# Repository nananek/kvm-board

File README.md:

# serial-km-emulator — CH9329 USB キーボード/マウスエミュレータ

MR-CH9329EMU-USB（マルツの CH9329 モジュール）の代替を JLCPCB の SMT 実装で作るための KiCad プロジェクトです。シリアル側とキーボード/マウス側の両方を USB Type-C にしています。

- 基板: 57.6 × 31.4 × 1.6 mm、2 層。実物の FRISK ケース内寸（67.0 × 32.4 mm）の左側に 0.5 mm ずつ逃がして置き、右側はラッチ張り出しとのクリアランスを残した寸法です
- 回路図: [docs/schematic.pdf](docs/schematic.pdf)
- データシートとシルクの対応: [docs/datasheets.md](docs/datasheets.md)
- 配線図: [docs/pcb_routing.png](docs/pcb_routing.png)（GND ベタを消して配線を見やすくしたもの）
- 部品: 21 点、10 種類。すべて JLCPCB の在庫部品（2026-10 時点）。このほかに、実装しないテストパッドを 2 点置いています
- ファームウェア不要。CH9329 の内蔵ファームで動きます

## 仕様

| 項目 | 内容 |
| --- | --- |
| 基板寸法 | 57.6 × 31.4 mm、t1.6 mm、2 層 |
| コネクタ | USB Type-C レセプタクル ×2（HRO TYPE-C-31-M-12）。どちらも基板左端、上下に 5.0 mm ずつ振り分け |
| J1 (SERIAL) | CH340N 経由の USB シリアル。制御側 PC に接続 |
| J2 (HID) | CH9329 の USB HID。操作対象の PC に接続 |
| 給電 | どちらの Type-C からでも給電可。BAT54WS でダイオード OR |
| シリアル | 9600 bps / 8N1（CH9329 出荷時設定） |
| 動作モード | CH9329 Mode 0（キーボード + マウス + カスタム HID の複合デバイス）、プロトコルモード |
| 表示 | ACT# の LED（HID 側の USB 設定完了で点灯） |
| テストパッド | TP1 (SET) / TP2 (GND)。CH9329 の設定変更用 |
| シルク | 表: 部品名とピン極性、裏: リポジトリの QR コード |

J1/J2 はどちらもデバイス側（CC に 5.1k の Rd）です。ホスト PC とは C-to-C でも C-to-A でも接続できます。充電器は接続しないでください。

基板裏面にはリポジトリ（<https://github.com/nananek/serial-km-emulator>）の QR コードをシルクで入れています。ケースに組み込む前ならスマートフォンで読み取れます。

## 回路

```
制御側 PC ──Type-C(J1)── CH340N ──UART── CH9329 ──Type-C(J2)── 操作対象 PC
                              (TXD→RXD, RXD←TXD, 9600 8N1)
```

- CH9329: 5 V 給電。V33 に 0.1 µF、VCC に 0.1 µF。内蔵発振なので水晶なし。
- CH340N: 5 V 給電。V3 に 0.1 µF。内蔵クロックなので水晶なし。
- ESD: 各ポートに USBLC6-2SC6。クランプ用の VBUS ピンは各ポートのローカル VBUS に接続し、100nF (C6/C7) で GND にデカップリング。
- 5 V は BAT54WS ×2 で OR 接続。IC には約 4.7 V が入ります（CH340N の最低 4.0 V、CH9329 の最低 3.7 V の範囲内）。
- CH9329 の MODE0/MODE1、CFG0/CFG1、DEF、RST は未接続。内蔵プルアップ/プルダウンで Mode 0・プロトコルモード・9600 bps になります。UP は 5 V 動作なので未接続です。
- SET はテストパッド TP1 に、GND は TP2 に引き出しています。

### 設定の書き換え（TP1 / TP2）

U1 の右側に 1.7 mm のテストパッドを 2 つ出しています。

| パッド | 接続 | 位置 |
| --- | --- | --- |
| TP1 | CH9329 SET (pin 11) | U1 の右側、左のパッド |
| TP2 | GND | U1 の右側、右のパッド |

ピッチは 2.54 mm です。ピンセットやジャンパワイヤで TP1 と TP2 を短絡したまま、J1 側から WCH の設定ツールで書き換えます。書き換えが終わったら短絡を外してください。通常動作では SET は内蔵プルアップのままです。

## 部品表

`fab/bom_jlcpcb.csv` がそのまま JLCPCB の BOM です。

| 記号 | 値 | パッケージ | LCSC | 備考 |
| --- | --- | --- | --- | --- |
| J1, J2 | TYPE-C-31-M-12 | USB-C 16P | C165948 | HRO |
| U1 | CH9329 | SOP-16 | C2838834 | WCH |
| U2 | CH340N | SOP-8 | C2977777 | WCH |
| D1, D2 | BAT54WS | SOD-323 | C22629 | ショットキー |
| D3, D4 | USBLC6-2SC6 | SOT-23-6 | C7519 | ESD |
| R1–R4 | 5.1k | 0603 | C23186 | CC 用 |
| R5 | 1k | 0603 | C21190 | LED 用 |
| C1–C4, C6, C7 | 100nF | 0603 | C14663 | 50V X7R |
| C5 | 10uF | 0805 | C15850 | 25V X5R |
| LED1 | KT-0603R | 0603 | C2286 | 赤 |

基本部品（C23186、C21190、C14663、C15850、C2286）以外の 5 種類は拡張部品です。拡張部品は 1 種類あたりの実装手数料がかかります。

## JLCPCB での発注

基板:

- 2 層、57.6 × 31.4 mm、t1.6 mm、FR-4、HASL、1 oz
- 最小配線幅/間隔 0.15/0.15 mm、ビア 0.5/0.3 mm。データ線のエスケープに 0.35/0.15 mm のビアも使っています。JLCPCB の標準能力内です。

実装:

- 表面のみ、21 点。
- アップロードするファイル:
  - ガーバー: `fab/serial-km-emulator-gerbers.zip`
  - BOM: `fab/bom_jlcpcb.csv`
  - CPL: `fab/cpl_jlcpcb.csv`
- ガーバー、ドリル、CPL はすべて基板左下を原点にした座標です（KiCad のドリル/配置原点を使用）。ガーバー zip と CPL はセットで再アップロードしてください。JLCPCB の部品ライブラリ向けの回転補正を入れてあります（SO-8/SO-16 +270°、SOT-23-6 +270°。Type-C、SOD-323、LED、0603 は回転補正なし）。Type-C は基板側でフットプリントを 180° 回して開口を左外側、SMT パッドを基板内側に置いています。CPL は JLC 側の原点に合わせて X を 1.571 mm 補正しており、出力は J1/J2 とも 270°、位置はどちらも X 3.7 mm（Y は J1 20.7 mm、J2 10.7 mm）です。補正値は `scripts/make_jlc_files.py` にあります。実装プレビューで向きを確認してください。

注意:

- Type-C コネクタ (C165948) はシェル固定タブが THT 形状ですが、JLCPCB の SMT 実装部品リストに含まれている部品です。SMT 実装で発注できます。
- Type-C の VBUS パッドから 0.5/0.3 mm のビアをパッドの外側に置き、B.Cu で引き回しています。ビアはパッド内ではないため、via-in-pad の DFM 指摘はありません。VBUS は 2 接点ずつパッドが重なっているので、ビアは各コネクタ 2 個です。
- ガーバーは KiCad 10 の既定（X2、4.6 フォーマット）です。

## フリスクケースへの組み込み

基板外形は、実物の FRISK ケースの内寸からラッチ張り出しの分だけ右側をまっすぐ切り落とした **57.6 × 31.4 mm** です。左上・左下・右下の角は **2 mm の 45° パンチカット**で落とし、右上だけ直角に残しています。角丸のルーター加工より外形カットを安くするためです。

### 実寸確認用シート

紙に印刷してケースとの寸法を確認するときは [docs/print_check_a4.pdf](docs/print_check_a4.pdf) を使ってください。

- A4 横、1:1。印刷時は「実際のサイズ / 100%」を選び、「用紙に合わせる」は使わないでください。
- グレーベタが基板、その外側の明るいグレーの帯がケース内壁との 0.5 mm クリアランスです。切り抜いてトレイに落とせます。
- 右側の網掛けがケースのラッチ張り出しです。基板のまっすぐな右辺は、この張り出しから 0.5 mm 離して置きます。
- 下部の 100 mm 目盛りが 100 mm になっていなければ、印刷倍率がずれています。
- `python3 scripts/gen_print_sheet.py` で作り直せます（基板外形は `serial-km-emulator.kicad_pcb` の Edge.Cuts から読みます）。

### ケース寸法

2026-10 に実物の FRISK ケースを実測しました。

- 内寸: **67.0 × 32.4 mm**
- ケース肉厚: **1.0 mm**
- ラッチ張り出しの奥行き: **8.4 mm**
- ラッチ張り出しの高さ: **21.4 mm**（反対側の開口部は 11.0 mm）

基板は内寸から 0.5 mm ずつ逃がしたうえで、右側のラッチ張り出し 8.4 mm を避けるために **57.6 × 31.4 mm** にしています。右辺はラッチ用の切り欠きやローブを作らず、1 本の直線カットです。左上・左下・右下の角は 2 mm の 45° パンチカットで落とし、右上だけ直角に残します。基板をトレイの左・上・下に 0.5 mm ずつ寄せると、右辺はラッチ張り出しから 0.5 mm 離れ、トレイ右側の 8.9 mm は空きます。

参考として、公開されている 3D モデル（[FRISK-CASE.zip](https://try3dcg.world.coocan.jp/files/FRISK-CASE.zip)、`FRISK_CASE1.stl`）は内トレイ 66.4 × 32.4 mm、張り出し 7.8 × 20.3 mm でした。実物は長辺が 0.6 mm 大きいため、実測値を優先しています。モデル配布ページは [3D PRINT用モデルデータ — FRISK CASE](https://try3dcg.world.coocan.jp/note/3dPrint/3dPrint.html#FRISK-CASE) です。

ロット差があるため、初回は必ず現物合わせで確認してください。

### 基板の向きと切り欠き

- 基板のまっすぐな右辺をケースのラッチ張り出し側に向け、基板をトレイの左・上・下に 0.5 mm ずつ寄せて置きます。右辺と張り出しの間に 0.5 mm の隙間ができます。ラッチ用の切り欠きはありません。ケースの角の丸みは、左上・左下・右下の 2 mm パンチカットで逃がします（右上は直角のままです）。
- J1 (SERIAL) と J2 (HID) はどちらも基板左端にあり、上から **10.7 mm** と **20.7 mm** の位置（基板の y 方向中心 15.7 mm から 5.0 mm ずつ、ピッチ 10.0 mm）です。口は基板端から **1.5 mm** 外へ出ます。2 つの口は蓋の切り欠きに収まる位置にあるため、蓋は削らず、トレイ左側壁に約 20 × 4 mm の開口を **壁を貫通するように** 1 か所開けてください（2 つの口が 1.06 mm しか離れていないため、開口も 1 つに繋がります）。
- 基板端はケース内壁から 0.5 mm、肉厚は 1.0 mm なので、1.5 mm の口はケース外面とほぼ面一になります。プラグは壁の切り欠きを通ってコネクタに届きます。
- 切り欠きの外側を 0.3 mm 程度面取りすると、プラグの樹脂（オーバーモールド）が当たりにくくなり、奥まで挿しやすくなります。
- 基板は左・上・下の 0.5 mm を保って固定してください。右側に寄せるとラッチ張り出しに当たります。
- 基板をトレイに置いたとき、コネクタの口は基板面から約 1.6〜4.9 mm の高さに来ます。ケース底面からの高さはスペーサーで調整してください。
- 固定用の穴はありません。両面テープやスポンジで固定します。基板とトレイの間に 1 mm 程度のスペーサーを入れると、プラグの挿入量を稼げます（高さ方向の調整で、左右の出寸法には影響しません）。
- 実機のケースで必ず確認してください。内寸が違う場合は基板外形を調整できます。

## 使い方

1. J2 (HID) を操作対象の PC に接続します。キーボード/マウスとして認識され、LED が点灯します。
2. J1 (SERIAL) を制御側の PC に接続します。CH340 の USB シリアル（Linux なら `/dev/ttyUSB0`）として見えます。
3. 9600 bps / 8N1 で CH9329 のプロトコルを送ります。

'A' を押して離す例（CH9329 プロトコル、チェックサムは全バイトの和の下位 8 bit）:

```python
import serial
s = serial.Serial("/dev/ttyUSB0", 9600, timeout=1)
s.write(bytes.fromhex("57 AB 00 02 08 00 00 04 00 00 00 00 00 10"))  # press A
s.write(bytes.fromhex("57 AB 00 02 08 00 00 00 00 00 00 00 00 0C"))  # release
```

プロトコルの詳細は WCH の CH9329 データシートと「CH9329 シリアル通信プロトコル」を参照してください。

## 設計メモ

- シリアル側と HID 側は独立した USB デバイスです。2 台の PC の GND がケーブル経由で共通になります。これは元の MR-CH9329EMU-USB と同じです。
- ESD 保護素子の VBUS ピンは、ダイオード OR の前の各ポートのローカル VBUS に接続しています。VBUS-GND 間の 100nF (C6/C7) は USBLC6 の近くに置き、ESD 時のクランプ電圧を安定させています。
- Type-C の 4 つの VBUS 接点はすべて接続しています。VBUS パッドは 2 接点ずつ重なっているので、各コネクタ 2 個の 0.5/0.3 mm ビアをパッドの外側に置き、B.Cu で引き回しています。
- GND は両面ベタ。USB の D+/D- は全速 12 Mbps なので、特にインピーダンス制御はしていません。
- 部品番号のテキストは U1/U2 以外はシルクから外しています（実装は CPL で行うため）。
- J1/J2 は 10.0 mm ピッチで、シェル同士は 1.06 mm 空いています。ライブラリのコートヤード（±5.32 mm）はシェル（8.94 mm）より広く、2 個並べると 0.64 mm 重なるため、`serial-km-emulator.kicad_dru` でこの 2 個の組み合わせだけコートヤードの重なりを許可しています。

## ファイル構成

```
serial-km-emulator.kicad_pro  KiCad プロジェクト（DRC ルール・ネットクラス込み）
serial-km-emulator.kicad_dru  J1/J2 のコートヤード重なりだけを許可する DRC ルール
serial-km-emulator.kicad_sch  回路図
serial-km-emulator.kicad_pcb  基板（配線・ベタ済み）
lib/kvm.kicad_sym             シンボルライブラリ
lib/KVM.pretty/               フットプリント（KiCad 公式ライブラリから取得）
fp-lib-table                  KVM.pretty の登録
sym-lib-table                 kvm.kicad_sym の登録
fab/                          ガーバー zip、BOM、CPL、KiCad 位置ファイル
docs/                         回路図 PDF、基板画像
scripts/                      設計データ生成スクリプト
AGENT.md                      エージェント向けの再生成・検証手順
```

## 再生成

KiCad 10 の `kicad-cli` と Python の `pcbnew` が必要です。

```sh
python3 scripts/gen_sch.py     # 回路図
python3 scripts/gen_pcb.py     # 基板（ゼロから生成）
./scripts/export_fab.sh        # ガーバー、BOM、CPL
./scripts/gen_docs_images.sh   # docs の基板画像
```

リポジトリの URL を変えたときだけ、`python3 scripts/make_repo_qr.py` で `scripts/repo_qr.txt` を作り直してください（`qrcode` パッケージが必要です）。基板の生成はこのテキストファイルを読むだけなので、通常のビルドに `qrcode` は要りません。

Docker しかない場合は `scripts/kicad.sh` 経由で同じコマンドを実行できます。手順は [AGENT.md](AGENT.md) にまとめています。

`serial-km-emulator.kicad_pcb` は `scripts/gen_pcb.py` が生成します。GUI で直接編集すると次回の生成で上書きされるので、変更はスクリプト側に入れてください。回路図も同様に `scripts/gen_sch.py` から生成しています。

## 検証

- ERC: 0 件
- DRC: 0 件（エラー・警告とも）
- 回路図のネットリストと基板のパッドネットは一致
- `kicad-cli pcb drc` / `kicad-cli sch erc` で確認済み

## ライセンス

MIT。詳細は [LICENSE](LICENSE) を参照してください。

基板の製造・実装・ケース加工は自己責任で行ってください。特に Type-C のシェル固定タブ、VBUS パッド外のビア、ケースの切り欠きは、発注前に各自の環境で確認してください。

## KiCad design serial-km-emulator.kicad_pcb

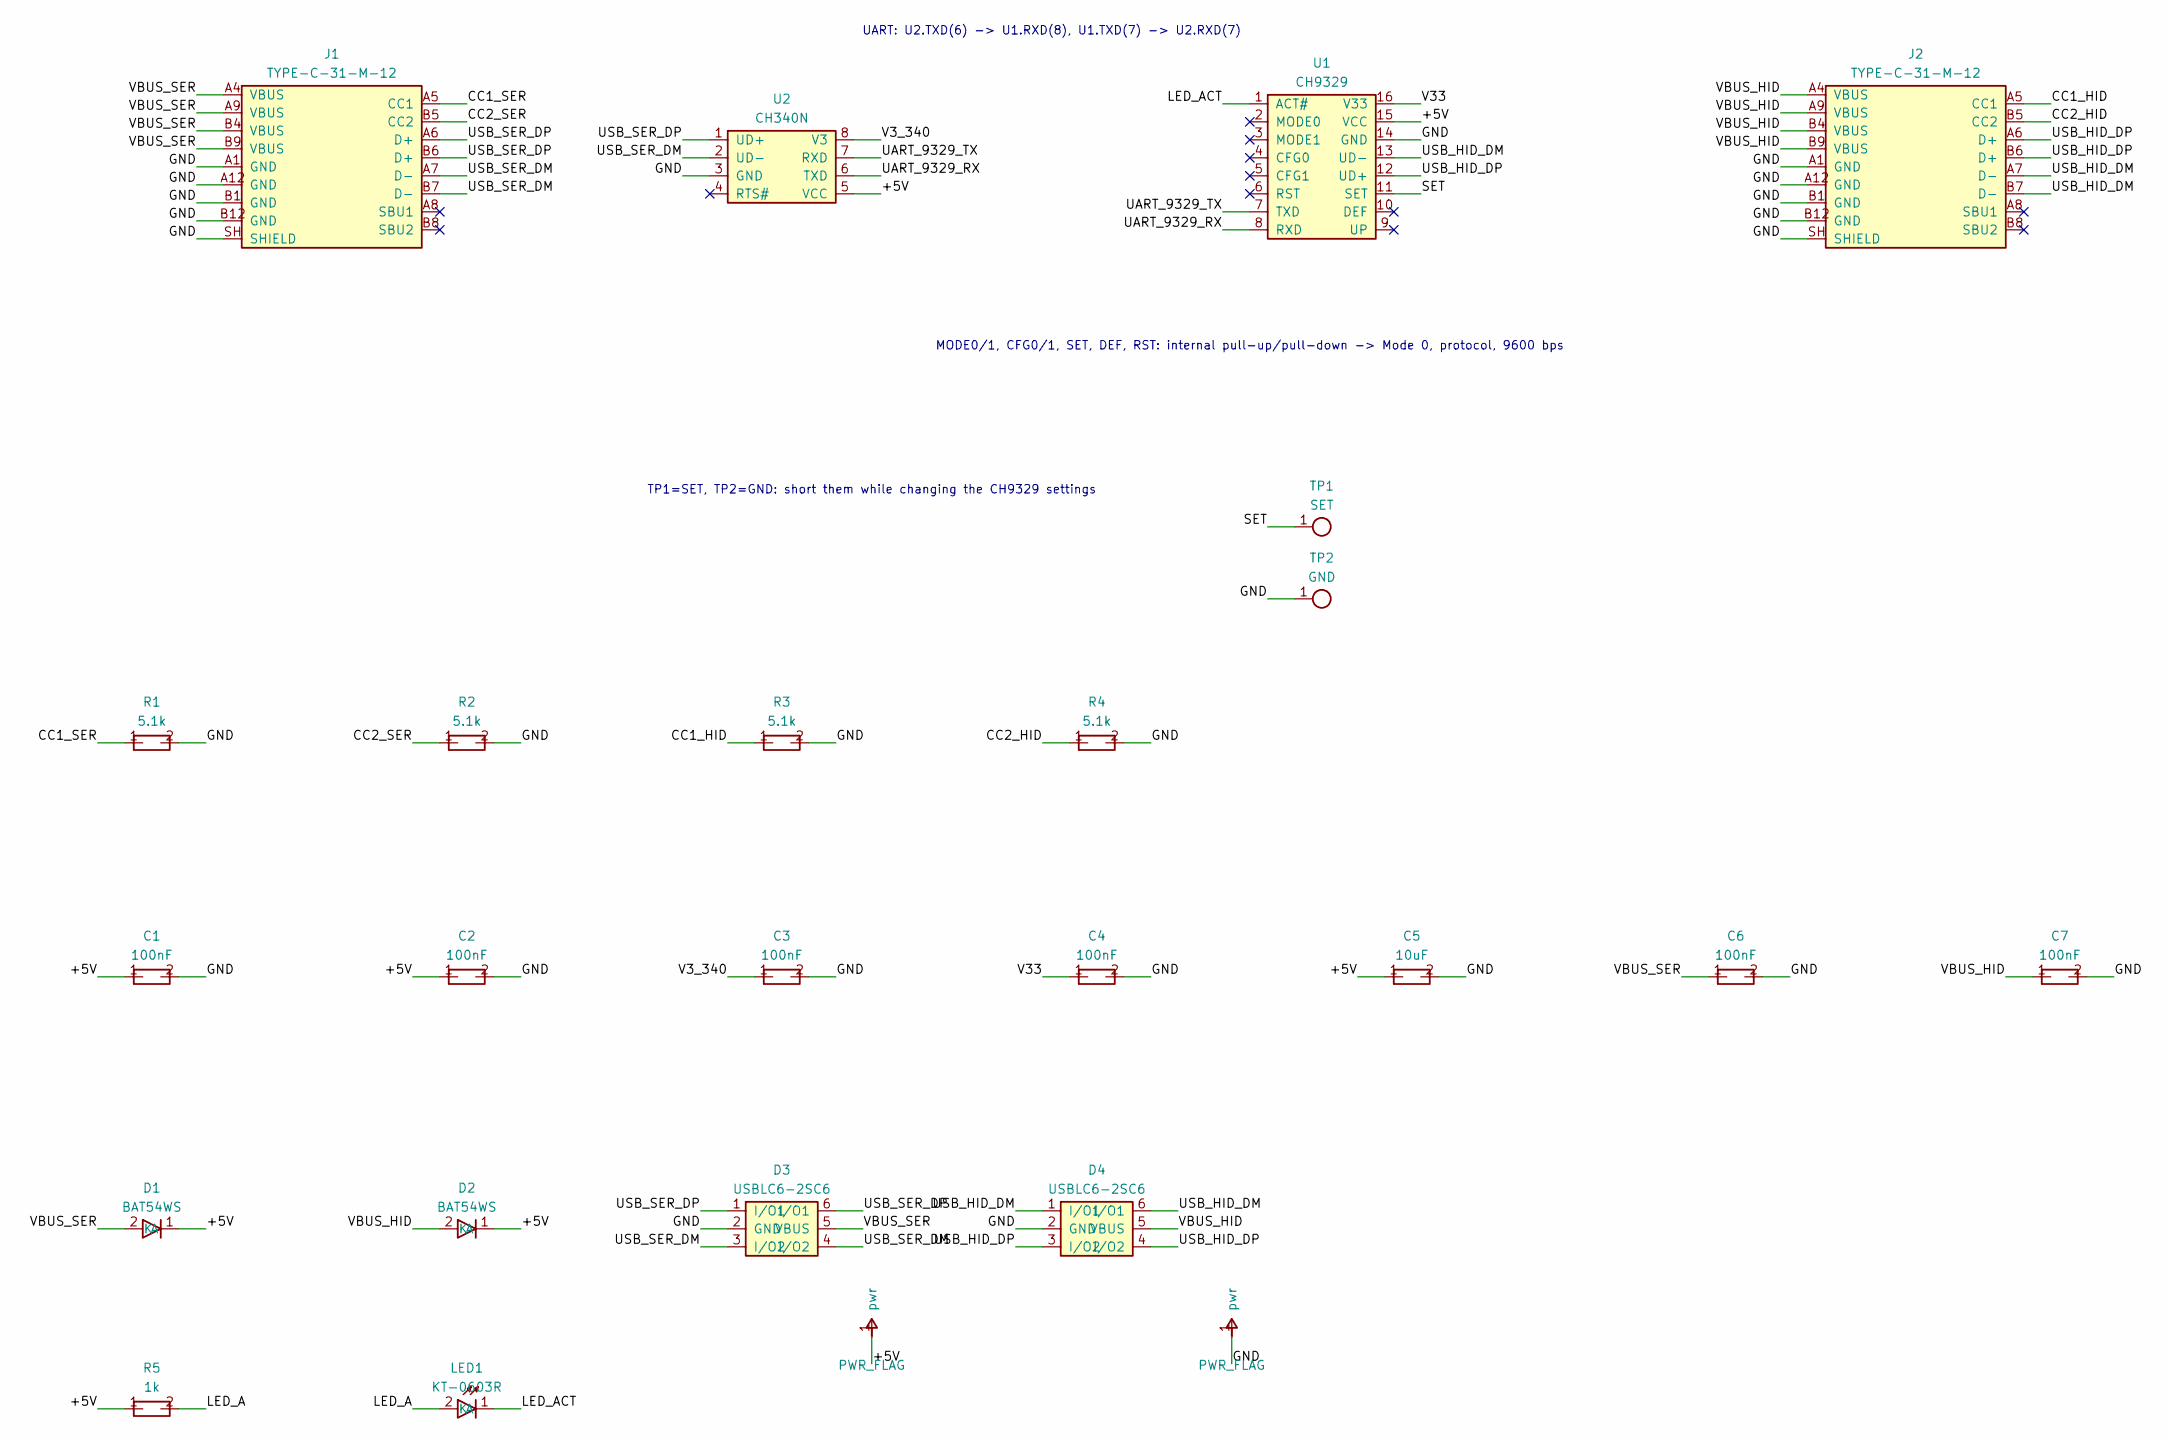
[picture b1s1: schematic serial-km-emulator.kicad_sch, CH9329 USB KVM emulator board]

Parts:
C1, C2, C3, C4, C6, C7: 100nF; C_0603_1608Metric; LCSC C14663
C5: 10uF; C_0805_2012Metric; LCSC C15850
D1, D2: BAT54WS; D_SOD-323; LCSC C22629
D3, D4: USBLC6-2SC6; SOT-23-6; LCSC C7519
J1, J2: TYPE-C-31-M-12; USB_C_Receptacle_HRO_TYPE-C-31-M-12; LCSC C165948
LED1: KT-0603R; LED_0603_1608Metric; LCSC C2286
R1, R2, R3, R4: 5.1k; R_0603_1608Metric; LCSC C23186
R5: 1k; R_0603_1608Metric; LCSC C21190
TP1: SET; TestPoint_1P
TP2: GND; TestPoint_1P
U1: CH9329; SO-16_3.9x9.9mm_P1.27mm; LCSC C2838834
U2: CH340N; SO-8_3.9x4.9mm_P1.27mm; LCSC C2977777

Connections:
+5V: C1.1, C2.1, C5.1, D1.1 (K), D2.1 (K), R5.1, U1.15 (VCC), U2.5 (VCC)
CC1_HID: J2.A5 (CC1), R3.1
CC1_SER: J1.A5 (CC1), R1.1
CC2_HID: J2.B5 (CC2), R4.1
CC2_SER: J1.B5 (CC2), R2.1
GND: C1.2, C2.2, C3.2, C4.2, C5.2, C6.2, C7.2, D3.2 (GND), D4.2 (GND), J1.A1 (GND), J1.A12 (GND), J1.B1 (GND), J1.B12 (GND), J1.SH (SHIELD), J2.A1 (GND), J2.A12 (GND), J2.B1 (GND), J2.B12 (GND), J2.SH (SHIELD), R1.2, R2.2, R3.2, R4.2, TP2.1, U1.14 (GND), U2.3 (GND)
LED_A: LED1.2 (A), R5.2
LED_ACT: LED1.1 (K), U1.1 (ACT#)
SET: TP1.1, U1.11 (SET)
UART_9329_RX: U1.8 (RXD), U2.6 (TXD)
UART_9329_TX: U1.7 (TXD), U2.7 (RXD)
USB_HID_DM: D4.1 (I/O1), D4.6 (I/O1), J2.A7 (D-), J2.B7 (D-), U1.13 (UD-)
USB_HID_DP: D4.3 (I/O2), D4.4 (I/O2), J2.A6 (D+), J2.B6 (D+), U1.12 (UD+)
USB_SER_DM: D3.3 (I/O2), D3.4 (I/O2), J1.A7 (D-), J1.B7 (D-), U2.2 (UD-)
USB_SER_DP: D3.1 (I/O1), D3.6 (I/O1), J1.A6 (D+), J1.B6 (D+), U2.1 (UD+)
V3_340: C3.1, U2.8 (V3)
V33: C4.1, U1.16 (V33)
VBUS_HID: C7.1, D2.2 (A), D4.5 (VBUS), J2.A4 (VBUS), J2.A9 (VBUS), J2.B4 (VBUS), J2.B9 (VBUS)
VBUS_SER: C6.1, D1.2 (A), D3.5 (VBUS), J1.A4 (VBUS), J1.A9 (VBUS), J1.B4 (VBUS), J1.B9 (VBUS)

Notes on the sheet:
UART: U2.TXD(6) -> U1.RXD(8), U1.TXD(7) -> U2.RXD(7)
MODE0/1, CFG0/1, SET, DEF, RST: internal pull-up/pull-down -> Mode 0, protocol, 9600 bps
TP1=SET, TP2=GND: short them while changing the CH9329 settings

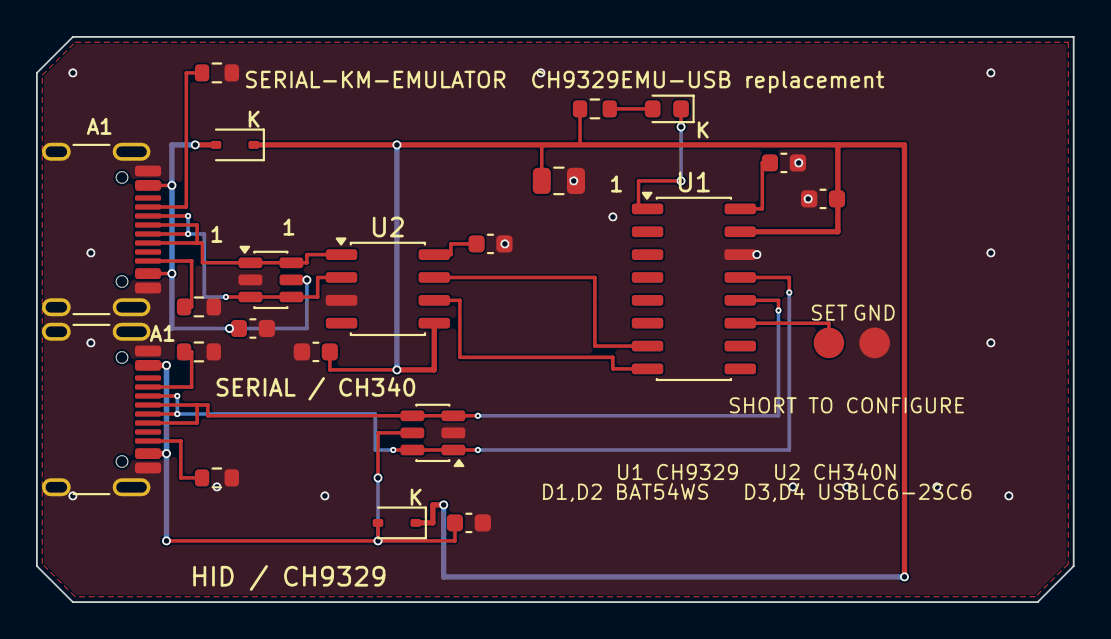
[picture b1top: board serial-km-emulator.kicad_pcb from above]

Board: 2 copper layers, 57.6 x 31.4 mm, 23 parts (0 on the bottom side), 19 nets.

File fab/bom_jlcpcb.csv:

Comment,Designator,Footprint,LCSC Part #
TYPE-C-31-M-12,"J1,J2",USB_C_Receptacle_HRO_TYPE-C-31-M-12,C165948
CH9329,U1,SO-16_3.9x9.9mm_P1.27mm,C2838834
CH340N,U2,SO-8_3.9x4.9mm_P1.27mm,C2977777
BAT54WS,"D1,D2",D_SOD-323,C22629
USBLC6-2SC6,"D3,D4",SOT-23-6,C7519
5.1k,"R1,R2,R3,R4",R_0603_1608Metric,C23186
1k,R5,R_0603_1608Metric,C21190
KT-0603R,LED1,LED_0603_1608Metric,C2286
100nF,"C1,C2,C3,C4,C6,C7",C_0603_1608Metric,C14663
10uF,C5,C_0805_2012Metric,C15850

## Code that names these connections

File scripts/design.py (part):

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         }),
    dict(ref="D1", value="BAT54WS", sym="D",
         fp="KVM:D_SOD-323", lcsc="C22629",
         pins={"2": "VBUS_SER", "1": P5V}),
    dict(ref="D2", value="BAT54WS", sym="D",
         fp="KVM:D_SOD-323", lcsc="C22629",
         pins={"2": "VBUS_HID", "1": P5V}),
    dict(ref="D3", value="USBLC6-2SC6", sym="USBLC6",
         fp="KVM:SOT-23-6", lcsc="C7519",
         pins={"1": "USB_SER_DP", "6": "USB_SER_DP",
               "3": "USB_SER_DM", "4": "USB_SER_DM",
               "2": GND, "5": "VBUS_SER"}),
    dict(ref="D4", value="USBLC6-2SC6", sym="USBLC6",
         fp="KVM:SOT-23-6", lcsc="C7519",
         # The two USBLC6 channels are electrically identical.  D4 uses
         # I/O1 for D- and I/O2 for D+ so the J2 fanout does not cross.
         pins={"1": "USB_HID_DM", "6": "USB_HID_DM",
               "3": "USB_HID_DP", "4": "USB_HID_DP",
               "2": GND, "5": "VBUS_HID"}),
    dict(ref="R1", value="5.1k", sym="R", fp="KVM:R_0603_1608Metric", lcsc="C23186",
         pins={"1": "CC1_SER", "2": GND}),
    dict(ref="R2", value="5.1k", sym="R", fp="KVM:R_0603_1608Metric", lcsc="C23186",
         pins={"1": "CC2_SER", "2": GND}),
    dict(ref="R3", value="5.1k", sym="R", fp="KVM:R_0603_1608Metric", lcsc="C23186",
         pins={"1": "CC1_HID", "2": GND}),
    dict(ref="R4", value="5.1k", sym="R", fp="KVM:R_0603_1608Metric", lcsc="C23186",
         pins={"1": "CC2_HID", "2": GND}),
    dict(ref="R5", value="1k", sym="R", fp="KVM:R_0603_1608Metric", lcsc="C21190",
         pins={"1": P5V, "2": "LED_A"}),
    dict(ref="LED1", value="KT-0603R", sym="LED", fp="KVM:LED_0603_1608Metric",
         lcsc="C2286", pins={"2": "LED_A", "1": "LED_ACT"}),
    dict(ref="C1", value="100nF", sym="C", fp="KVM:C_0603_1608Metric", lcsc="C14663",
         pins={"1": P5V, "2": GND}),
    dict(ref="C2", value="100nF", sym="C", fp="KVM:C_0603_1608Metric", lcsc="C14663",
         pins={"1": P5V, "2": GND}),
    dict(ref="C3", value="100nF", sym="C", fp="KVM:C_0603_1608Metric", lcsc="C14663",
         pins={"1": "V3_340", "2": GND}),
    dict(ref="C4", value="100nF", sym="C", fp="KVM:C_0603_1608Metric", lcsc="C14663",
         pins={"1": "V33", "2": GND}),
    dict(ref="C5", value="10uF", sym="C", fp="KVM:C_0805_2012Metric", lcsc="C15850",
         pins={"1": P5V, "2": GND}),
    dict(ref="C6", value="100nF", sym="C", fp="KVM:C_0603_1608Metric", lcsc="C14663",
         pins={"1": "VBUS_SER", "2": GND}),
    dict(ref="C7", value="100nF", sym="C", fp="KVM:C_0603_1608Metric", lcsc="C14663",
         pins={"1": "VBUS_HID", "2": GND}),
    # Bare test pads: TP1 = CH9329 SET, TP2 = GND.  Not fitted parts.
    dict(ref="TP1", value="SET", sym="TP", fp="KVM:TestPoint_1P", lcsc="",
         fitted=False, pins={"1": "SET"}),
    dict(ref="TP2", value="GND", sym="TP", fp="KVM:TestPoint_1P", lcsc="",
         fitted=False, pins={"1": GND}),
]
PARTS = p

# UART cross connection
assert PARTS[2]["pins"]["7"] == "UART_9329_TX"   # U1 TXD -> CH340 RXD
assert PARTS[3]["pins"]["7"] == "UART_340_RX"
assert PARTS[2]["pins"]["8"] == "UART_9329_RX"
assert PARTS[3]["pins"]["6"] == "UART_340_TX"
# same net on both sides: rename so labels match
for part in PARTS:
    for k, v in list(part["pins"].items()):
        if v == "UART_340_RX":
            part["pins"][k] = "UART_9329_TX"
        elif v == "UART_340_TX":
            part["pins"][k] = "UART_9329_RX"

NETS = sorted({n for part in PARTS for n in part["pins"].values() if n})

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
